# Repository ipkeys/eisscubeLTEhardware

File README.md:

# eisscubeLTEhardware
EISScube v3.0 LTE hardware design

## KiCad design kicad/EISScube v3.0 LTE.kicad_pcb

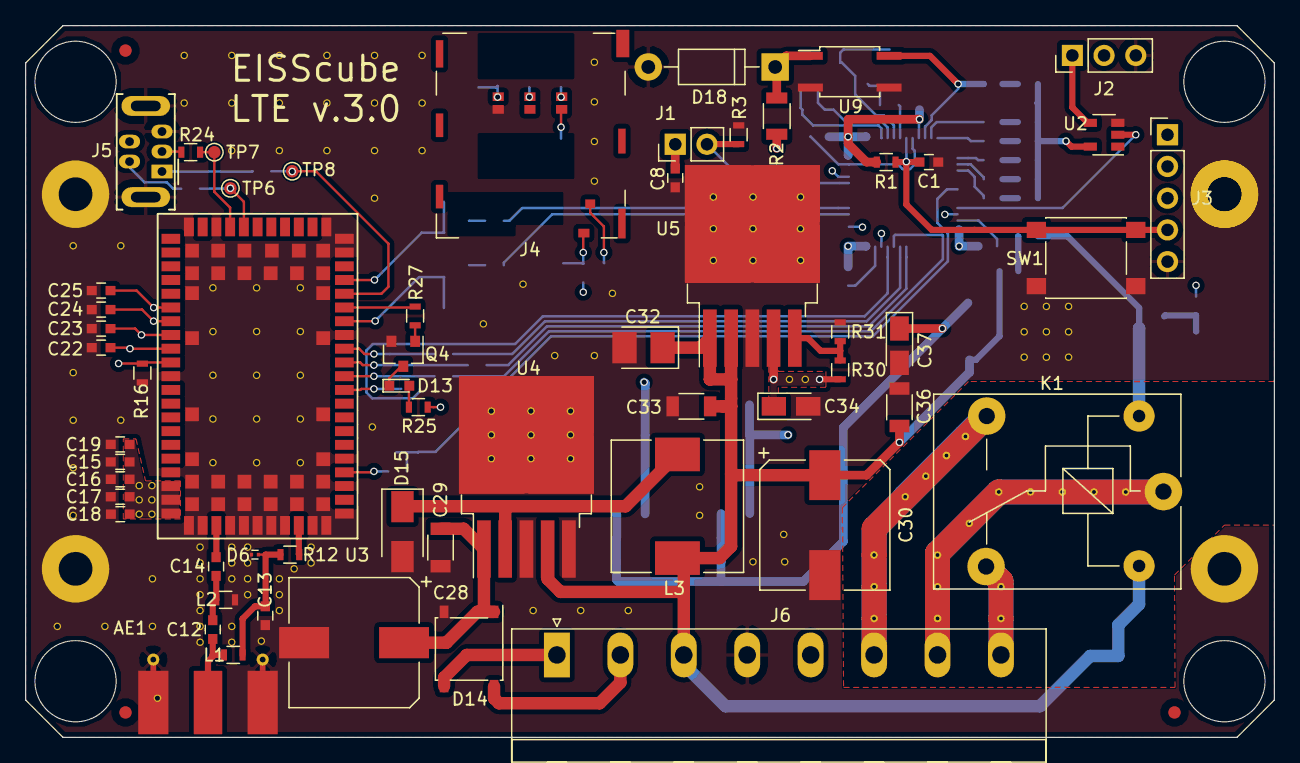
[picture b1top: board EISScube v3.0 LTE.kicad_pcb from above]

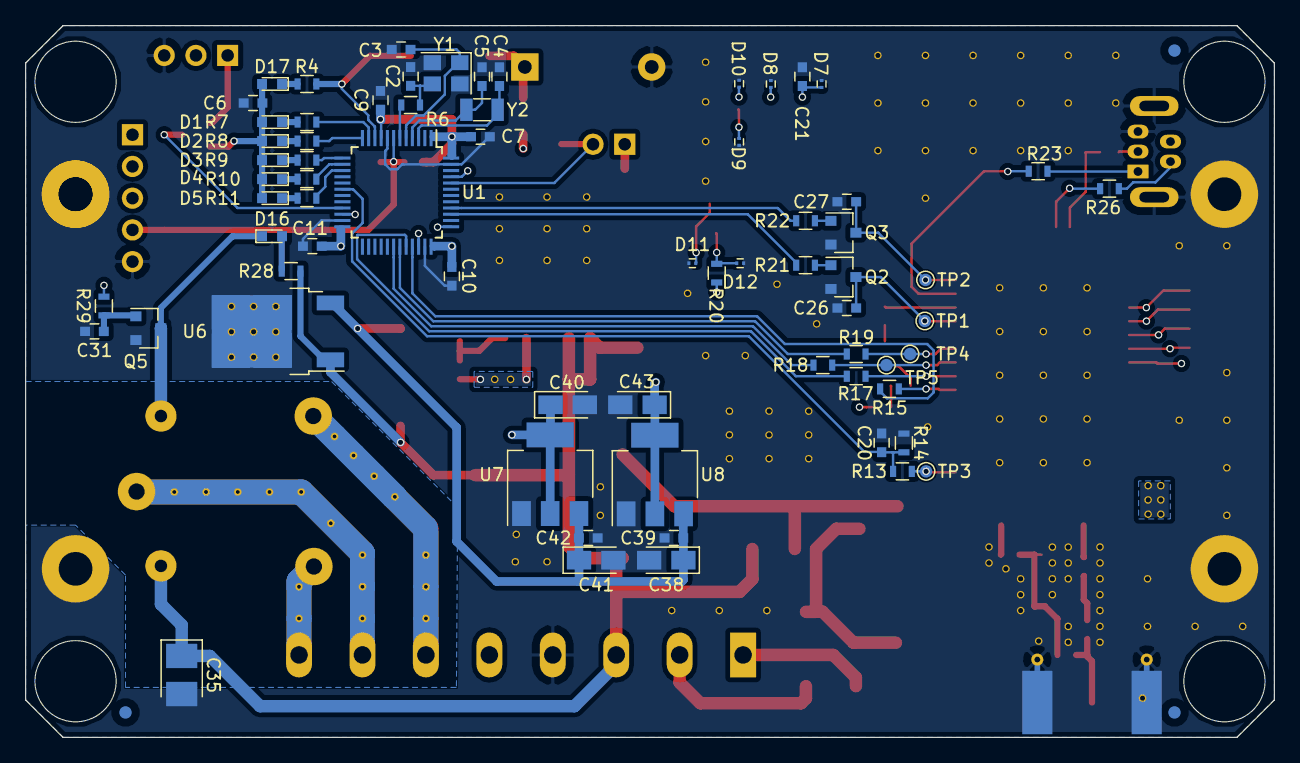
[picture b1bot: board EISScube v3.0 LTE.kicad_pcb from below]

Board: 4 copper layers, 100.0 x 57.0 mm, 132 parts (71 on the bottom side), 81 nets.

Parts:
AE1: Antenna_Shield; Molex_SMA_Jack_Edge_Mount
C1, C6, C7, C8, C9, C10, C11, C18, C20, C21, C31: 104K; C_0603
C2, C3, C4, C5: 220J; C_0603
C12: 330J; C_0603
C13: 270J; C_0603
C14, C15: 150J; C_0603
C16: 680J; C_0603
C17: 103K; C_0603
C19, C39, C42: 105K; C_0603
C22, C23, C24, C25, C26, C27: 470J; C_0603
C28: 220uF 35V; CP_Elec_10x10.5
C29, C33, C36: 105K; C_1206
C30: 680uF 16V; CP_Elec_10x10.5
C32, C35: 106K 16V; CP_Tantalum_Case-B_EIA-3528-21_Reflow
C34, C37, C38, C40, C41, C43: 106K 6V3; CP_Tantalum_Case-A_EIA-3216-18_Reflow
D1, D2, D3, D4, D5: blue; LED_0603
D6, D7, D8, D9, D10, D11, D12: VBUS05B1-SD0; L_0201
D13, D16, D17: red; LED_0603
D14: MBL104S; Diode_Bridge_MBLS
D15: B120-E3; D_SMA
D18: 1N4001; D_DO-41_SOD81_P10.16mm_Horizontal
FID1, FID2, FID3, FID4, FID5, FID6: Fiducial; Fiducial_1mm_Dia_2mm_Outer
J1: Boot; Pin_Header_Straight_1x02_Pitch2.54mm
J2: UART; Pin_Header_Straight_1x03_Pitch2.54mm
J3: JTag; Socket_Strip_Straight_1x05_Pitch2.54mm
J4: SIM_Card_w_det_sw; SIM_Card_Hirose_KP10S-SF-PEJ-812
J5: USB_B_Mini; USB_Micro-B_Molex-5022370517_Vertical
J6: Screw_Terminal_01x08; PhoenixContact_MSTBA-G_08x5.08mm_Angled
K1: SANYOU_SRD_Form_C; Relay_SPDT_SANYOU_SRD_Series_Form_C
L1: 68nH; L_0603
L2: 39nH; L_0603
L3: 150uH; L_10.4x10.4_H4.8
Q2, Q3, Q4, Q5: GSM3612PJZF; SOT-23
R1: 100K; R_0603
R2: 1K; R_1206
R3: 510R; R_0603
R4, R7, R8, R9, R10, R11, R20, R21, R22, R25, R27, R28, R29: 1K; R_0603
R6: 240R; R_0603
R12, R13, R14: 10K; R_0603
R15, R17, R18, R19, R23, R24, R26: 0R; R_0603
R16: 470K; R_0603
R30: 30K; R_0603
R31: 15K; R_0603
SW1: Reset; SW_SPST_PTS645
TP1, TP2, TP3, TP4, TP5, TP6, TP7, TP8: Test_Point; Test_Point_Pad_d1.0mm
U1: STM32L051C8Tx; LQFP-48_7x7mm_Pitch0.5mm
U2: SN74LV1T34DBVR; SOT-23-5
U3: U-Blox-SARA-R4; SARA-R4-96
U4: LM2576HVS-12; TO-263-5_TabPin3
U5: MIC29302WU-TR; TO-263-5_TabPin6
U6: L7805; TO-252-2
U7: LM1117-3.3; SOT-223-3_TabPin2
U8: LM1117-1.8; SOT-223-3_TabPin2
U9: LTV-357T; SO-4_4.4x3.6mm_Pitch2.54mm
Y1: 12MHz; Crystal_SMD_3225-4pin_3.2x2.5mm
Y2: 32.768KHz; Crystal_SMD_3215-2pin_3.2x1.5mm

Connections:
24VAC-1: D14.3, J6.1
24VAC-2: D14.4, J6.2
+1V8: C7.1, C8.1, C9.1, C10.1, C11.1, C43.1, J1.1, J3.1, R1.1, U1.1, U1.9, U1.24, U1.36, U1.48, U8.2
+3V3: C6.1, C40.1, D1.2, D2.2, D3.2, D4.2, D5.2, D17.2, U2.5, U7.2
+3V8: C15.1, C16.1, C17.1, C18.1, C19.1, C34.1, R25.2, R30.2, U3.51, U3.52, U3.53, U5.4
+12V: C30.1, C32.1, C33.1, C35.1, C36.1, J6.3, K1.5, L3.2, R28.2, U4.4, U5.1, U5.2, U6.1
/EISScube-cl/CTS: R17.1, U3.11
/EISScube-cl/GPIO1: R27.1, U3.16
/EISScube-cl/PWR_ON: C26.1, Q2.3, TP1.1, U3.15
/EISScube-cl/RESET_N: C27.1, Q3.3, TP2.1, U3.18
/EISScube-cl/RST: R15.1, U3.10
/EISScube-cl/RXD: R19.1, TP4.1, U3.13
/EISScube-cl/SIM_CLK: C25.1, D10.2, J4.C3, U3.38
/EISScube-cl/SIM_DTK: D11.2, J4.S1, R16.1, U3.42
/EISScube-cl/SIM_IO: C24.1, D9.2, J4.C7, U3.39
/EISScube-cl/SIM_RST: C23.1, D8.2, J4.C2, U3.40
/EISScube-cl/TXD: R18.1, TP5.1, U3.12
/EISScube-cl/VSIM: C21.1, C22.1, D7.2, J4.C1, U3.41
/EISScube-cl/VUSB: R23.2, TP8.1, U3.17
/EISScube-cl/V_INT: R13.1, R20.2, TP3.1, U3.4
/EISScube-mc/BOOT0: J1.2, R3.1, U1.44
/EISScube-mc/RX_H: J2.2, U1.22
/EISScube-mc/SWCLK: J3.3, U1.37
/EISScube-mc/SWDIO: J3.2, U1.34
/EISScube-mc/TX_H: J2.1, U2.4
/EISScube-mc/UART1_TX: U1.21, U2.2
/EISScube-pw/+5V: C37.1, C38.1, C39.1, C41.1, C42.1, U6.3, U7.3, U8.3
/EISScube-pw/COM: J6.7, K1.1
/EISScube-pw/NC: J6.6, K1.3
/EISScube-pw/NO: J6.8, K1.4
CL_CTS: R17.2, U1.32
CL_POWER: R21.1, U1.39
CL_RESET: R22.1, U1.40
CL_RTS: R15.2, U1.33
CL_RXD: R19.2, U1.31
CL_TXD: R18.2, U1.30
CL_V_INT: C20.1, R13.2, R14.1, U1.18
GND: AE1.2, C1.1, C2.2, C3.2, C4.2, C5.2, C6.2, C7.2, C8.2, C9.2, C10.2, C11.2, C13.1, C15.2, C16.2, C17.2, C18.2, C19.2, C20.2, C21.2, C22.2, C23.2, C24.2, C25.2, C26.2, C27.2, C28.2, C29.2, C30.2, C31.2, C32.2, C33.2, C34.2, C35.2, C36.2, C37.2, C38.2, C39.2, C40.2, C41.2, C42.2, C43.2, D6.1, D7.1, D8.1, D9.1, D10.1, D11.1, D12.1, D14.2, D15.2, D18.2, J2.3, J3.5, J4.C5, J5.5, J5.6, J6.4, L2.2, Q2.2, Q3.2, Q4.2, Q5.2, R3.2, R14.2, R16.2, R31.1, SW1.1, U1.8, U1.23, U1.35, U1.47, U2.3, U3.1, U3.3, U3.5, U3.14, U3.20, U3.21, U3.22, U3.30, U3.32, U3.43, U3.50, U3.54, U3.55, U3.57, U3.58, U3.59, U3.60, U3.61, U3.63, U3.64, U3.65, U3.66, U3.67, U3.68, U3.69, U3.70, U3.71, U3.72, U3.73, U3.74, U3.75, U3.76, U3.77, U3.78, U3.79, U3.80, U3.81, U3.82, U3.83, U3.84, U3.85, U3.86, U3.87, U3.88, U3.89, U3.90, U3.91, U3.92, U3.93, U3.94, U3.95, U3.96, U4.3, U4.5, U5.3, U5.6, U6.2, U7.1, U8.1, U9.2, U9.3, Y1.2, Y1.4
INPUT: J6.5, R2.1
NRST: C1.2, J3.4, R1.2, SW1.2, U1.7
unnamed: AE1.1, C12.1, L1.2
unnamed: C2.1, R6.2, Y1.3
unnamed: C3.1, U1.5, Y1.1
unnamed: C4.1, U1.3, Y2.1
unnamed: C5.1, U1.4, Y2.2
unnamed: C12.2, C14.1, L2.1
unnamed: C13.2, D6.2, L1.1, R12.1
unnamed: C14.2, U3.56
unnamed: C28.1, C29.1, D14.1, U4.1
unnamed: C31.1, Q5.1, R29.1
unnamed: D1.1, R7.1
unnamed: D2.1, R8.1
unnamed: D3.1, R9.1
unnamed: D4.1, R10.1
unnamed: D5.1, R11.1
unnamed: D12.2, J4.S2, R20.1
unnamed: D13.1, Q4.3
unnamed: D13.2, R25.1
unnamed: D15.1, L3.1, U4.2
unnamed: D16.1, K1.2, Q5.3
unnamed: D16.2, R28.1
unnamed: D17.1, R4.2
unnamed: D18.1, R2.2, U9.1
unnamed: J5.1, R23.1
unnamed: J5.2, R26.1
unnamed: J5.3, R24.1
unnamed: Q2.1, R21.2
unnamed: Q3.1, R22.2
unnamed: Q4.1, R27.2
unnamed: R4.1, U1.10, U9.4
unnamed: R6.1, U1.6
unnamed: R7.2, U1.11
unnamed: R8.2, U1.12
unnamed: R9.2, U1.13
unnamed: R10.2, U1.14
unnamed: R11.2, U1.15
unnamed: R12.2, U3.62
unnamed: R24.2, TP7.1, U3.29
unnamed: R26.2, TP6.1, U3.28
unnamed: R30.1, R31.2, U5.5
RELAY: R29.2, U1.45

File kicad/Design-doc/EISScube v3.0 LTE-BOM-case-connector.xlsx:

Source: | EISScube v3.0 LTE.sch
Date: | Wednesday, April 18, 2018 'PMt' 01:15:05 PM
Tool: | Eeschema 4.0.7
Component Count: | 126
Ref | Qnty | Value | Footprint | Description
AE1, | 1 | Antenna_Shield | Connectors_Molex:Molex_SMA_Jack_Edge_Mount | SMA Jack (edge mount)
C1, C7, C8, C9, C10, C11, C6, C21, C18, C20, C31, | 11 | 104K | Capacitors_SMD:C_0603 | Unpolarized capacitor
C4, C5, C2, C3, | 4 | 220J | Capacitors_SMD:C_0603 | Unpolarized capacitor
C12, | 1 | 330J | Capacitors_SMD:C_0603 | Unpolarized capacitor
C13, | 1 | 270J | Capacitors_SMD:C_0603 | Unpolarized capacitor
C14, C15, | 2 | 150J | Capacitors_SMD:C_0603 | Unpolarized capacitor
C16, | 1 | 680J | Capacitors_SMD:C_0603 | Unpolarized capacitor
C17, | 1 | 103K | Capacitors_SMD:C_0603 | Unpolarized capacitor
C19, C39, C42, | 3 | 105K | Capacitors_SMD:C_0603 | Unpolarized capacitor
C27, C26, C22, C23, C24, C25, | 6 | 470J | Capacitors_SMD:C_0603 | Unpolarized capacitor
C28, | 1 | 220uF 35V | Capacitors_SMD:CP_Elec_10x10.5 | Polarised capacitor
C30, | 1 | 470uF 16V | Capacitors_SMD:CP_Elec_10x10.5 | Polarised capacitor
C32, C35, | 2 | 106K 16V | Capacitors_Tantalum_SMD:CP_Tantalum_Case-B_EIA-3528-21_Reflow | Polarised capacitor
C34, C37, C38, C40, C41, C43, | 6 | 106K 6V3 | Capacitors_Tantalum_SMD:CP_Tantalum_Case-A_EIA-3216-18_Reflow | Polarised capacitor
C36, C33, C29, | 3 | 105K | Capacitors_SMD:C_1206 | Unpolarized capacitor
D1, D2, D3, D4, D5, | 5 | blue | LEDs:LED_0603 | LED generic
D6, D7, D8, D9, D10, D11, D12, | 7 | VBUS05B1-SD0 | Diodes_SMD:D_0603 | ESD Suppressors / TVS Diodes BiSy Sngl Line 5.5V ESD Prot Diode 16kV
D14, | 1 | MBL104S | Diodes_SMD:Diode_Bridge_MBLS | Diode Bridge
D15, | 1 | B120-E3 | Diodes_SMD:D_SMA | Surface Mount Schottky Barrier Rectifier
D17, D13, D16, | 3 | red | LEDs:LED_0603 | LED generic
D18, | 1 | 1N4001 | Diodes_THT:D_DO-41_SOD81_P10.16mm_Horizontal | Diod generic
J1, | 1 | Boot | Pin_Headers:Pin_Header_Straight_1x02_Pitch2.54mm | Generic connector, single row, 01x02
J2, | 1 | UART | Pin_Headers:Pin_Header_Straight_1x03_Pitch2.54mm | Generic connector, single row, 01x03
J3, | 1 | JTag | Socket_Strips:Socket_Strip_Straight_1x05_Pitch2.54mm | Generic connector, single row, 01x05
J4, | 1 | SIM_Card_w_det_sw | EISScube_LTE:SIM_Card_Hirose_KP10S-SF-PEJ-812 | SIM Card push-push holder with detect switch
J5, | 1 | USB_B_Mini | EISScube_LTE:USB_Micro-B_Molex-5022370517_Vertical | USB Mini Type B connector
J6, | 1 | Screw_Terminal_01x08 | Connectors_Phoenix:PhoenixContact_MSTBA-G_08x5.08mm_Angled | Phoenix Contact MSTBA-G_08
K1, | 1 | SANYOU_SRD_Form_C | Relays_THT:Relay_SPDT_SANYOU_SRD_Series_Form_C | Relay Song Chuan 833H-1C-C-12VDC
L1, | 1 | 68nH | Inductors_SMD:L_0603 | Inductor generic
L2, | 1 | 39nH | Inductors_SMD:L_0603 | Inductor generic
L3, | 1 | 150uH | Inductors_SMD:L_10.4x10.4_H4.8 | Inductor power
Q3, Q4, Q2, Q5, | 4 | GSM3612PJZF | TO_SOT_Packages_SMD:SOT-23 | Transistor N-MOSFETwith substrate diode (general)
R1, | 1 | 100K | Resistors_SMD:R_0603 | Resistor generic
R2, | 1 | 1K | Resistors_SMD:R_1206 | Resistor generic
R3, | 1 | 510R | Resistors_SMD:R_0603 | Resistor generic
R6, | 1 | 240R | Resistors_SMD:R_0603 | Resistor generic
R7, R8, R9, R10, R11, R4, R21, R22, R27, R25, R20, R29, R28, | 13 | 1K | Resistors_SMD:R_0603 | Resistor generic
R12, R13, R14, | 3 | 10K | Resistors_SMD:R_0603 | Resistor generic
R16, | 1 | 470K | Resistors_SMD:R_0603 | Resistor generic
R24, R26, R23, R19, R18, R17, R15, | 7 | 0R | Resistors_SMD:R_0603 | Resistor generic
R30, | 1 | 30K | Resistors_SMD:R_0603 | Resistor generic
R31, | 1 | 15K | Resistors_SMD:R_0603 | Resistor generic
SW1, | 1 | Reset | Buttons_Switches_SMD:SW_SPST_PTS645 | Push button switch, generic, 4 pins
TP1, TP2, TP7, TP6, TP8, TP3, TP4, TP5, | 8 | Test_Point | Connectors_TestPoints:Test_Point_Pad_d1.0mm | test point
U1, | 1 | STM32L051C8Tx | Housings_QFP:LQFP-48_7x7mm_Pitch0.5mm | Core: ARM Cortex-M0+, Package: LQFP48, Flash: 32 kB, RAM: 8 kB, Frequency: 32 M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
U2, | 1 | SN74LV1T34DBVR | TO_SOT_Packages_SMD:SOT-23-5 | Single Power Supply Single Buffer GATE CMOS Logic Level Shifter
U3, | 1 | U-Blox-SARA-R4 | EISScube_LTE:SARA-R4-96 | LTE Cat M1/NB1 and EGPRS modules - SARA-R410M-02B-00, SARA-R410M-01B-00, SARA-R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
U4, | 1 | LM2576HVS-12 | TO_SOT_Packages_SMD:TO-263-5_TabPin3 | TO-263, 12V 3A Step-Down VR High Voltage Input
U5, | 1 | MIC29302WU-TR | TO_SOT_Packages_SMD:TO-263-5_TabPin6 | High-Current Low Dropout Regulators
U6, | 1 | L7805 | TO_SOT_Packages_SMD:TO-252-2 | Positive 1.5A 35V Linear Regulator, Fixed Output 5V
U7, | 1 | LM1117-3.3 | TO_SOT_Packages_SMD:SOT-223-3_TabPin2 | 800mA Low-Dropout Linear Regulator, 3.3V fixed output
U8, | 1 | LM1117-1.8 | TO_SOT_Packages_SMD:SOT-223-3_TabPin2 | 800mA Low-Dropout Linear Regulator, 1.8V fixed output
U9, | 1 | LTV-357T | Housings_SOIC:SO-4_4.4x3.6mm_Pitch2.54mm | DC Optocoupler, Vce 80V, CTR 50%
Y1, | 1 | 12MHz | Crystals:Crystal_SMD_3225-4pin_3.2x2.5mm | Four pin crystal (GND on pins 2 and 4), e.g. in SMD package
Y2, | 1 | 32.768KHz | Crystals:Crystal_SMD_3215-2pin_3.2x1.5mm | Two pin crystal
External | 1 | Screw_Terminal_01x08 second part | PhoenixContact_MSTB 2,5/ 2-ST-5,08 | Plug component, Screw connection with tension sleeve Phoenix Contact MSTB 2-ST-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
External | 1 | Case | RITEC Enclosures - RL6015 | Clousure case (need to ask for customization - make a 4 holes in bottom part)

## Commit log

2018-04-05 first version for internal review
2018-04-18 Changes for enclosure case
2018-04-18 checking
2018-04-25 add visual references are called “fiducials“ on board for PnP machine
2018-05-04 changes for new case RL6015
2018-05-04 new spec and 3D models
2018-05-07 sent to Chin-Tec
2018-05-08 moved LEDs on bottom side. Created a custome bottom part of enclosure RL6015
2018-05-11 new specs for LED and 2D models
2018-10-21 new docs
2018-11-28 3D model of box and docs
2022-11-02 migration to new version of KiCAD v.6.x
2022-11-07 backups
2024-02-21 backup before to migrate to KILN
